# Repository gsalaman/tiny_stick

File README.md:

# Tiny Stick
Hardware design for a line of 8 surface-mount WS2812C LEDs

# Configurations
## UNO (or other external processor)
You can use the 8 RGB LEDs with any Arduino capable processor.  Supply 5v, Gnd, and your Data Input via the "external input" ports on the bottom-left of the board.

You can chain together multiple sticks by using the "external output" port on the bottom-right.
## Tiny85
The board can also be populated with a tiny85.  Recommended configuration is to put a socket on U1 (top left) as to allow for the processor to be removed and programmed.  This processor connects to the data input line via Ardiuno Data pin 3 (physical pin 2 on the tiny).

There is also space on the board for a potentiometer.  The two sides are connected to power and ground, and the middle is connected to arduino pin 2 (physical pin 7).

Finally, there is a push-button, connected to Arduino pin 0 (phyical pin 5).  This input is pulled-up.

## Using External 5v Power with Tiny85
You can connect +5v and GND to the "external input" pins on the bottom left of the board to power the Tiny and LEDs.  This input is *not* gated by the power swiitch.

## Using Coin Cell
The back of the board has a spot for a coin cell holder, which can provide power to the Tiny and LEDs.  To enable this:
* connect the middle and bottom pins of the "input power select" block, either via a jumper or solder blob.
* populate the "internal power" switch on the bottom of the board (for switch control), or, if you want it "always on", put a solder jumper between the left and middle pins.

## Using the 9v (vin) input)
You can connect a 9v battery (or anything greather than 6v) to the Vin jumpers on the bottom left of the board.  This input goes through a voltage regulator to provide 5v.  To enable this:
* connect the top and middle pins of the "input power select" block, either via a jumper or solder blob.
* populate the "internal power" switch on the bottom of the board (for switch control), or, if you want it "always on", put a solder jumper between the left and middle pins.

One note:  since the switch is after the voltage regulator, the 9v battery will *always* be powering on the voltage regulator...not an ideal design.

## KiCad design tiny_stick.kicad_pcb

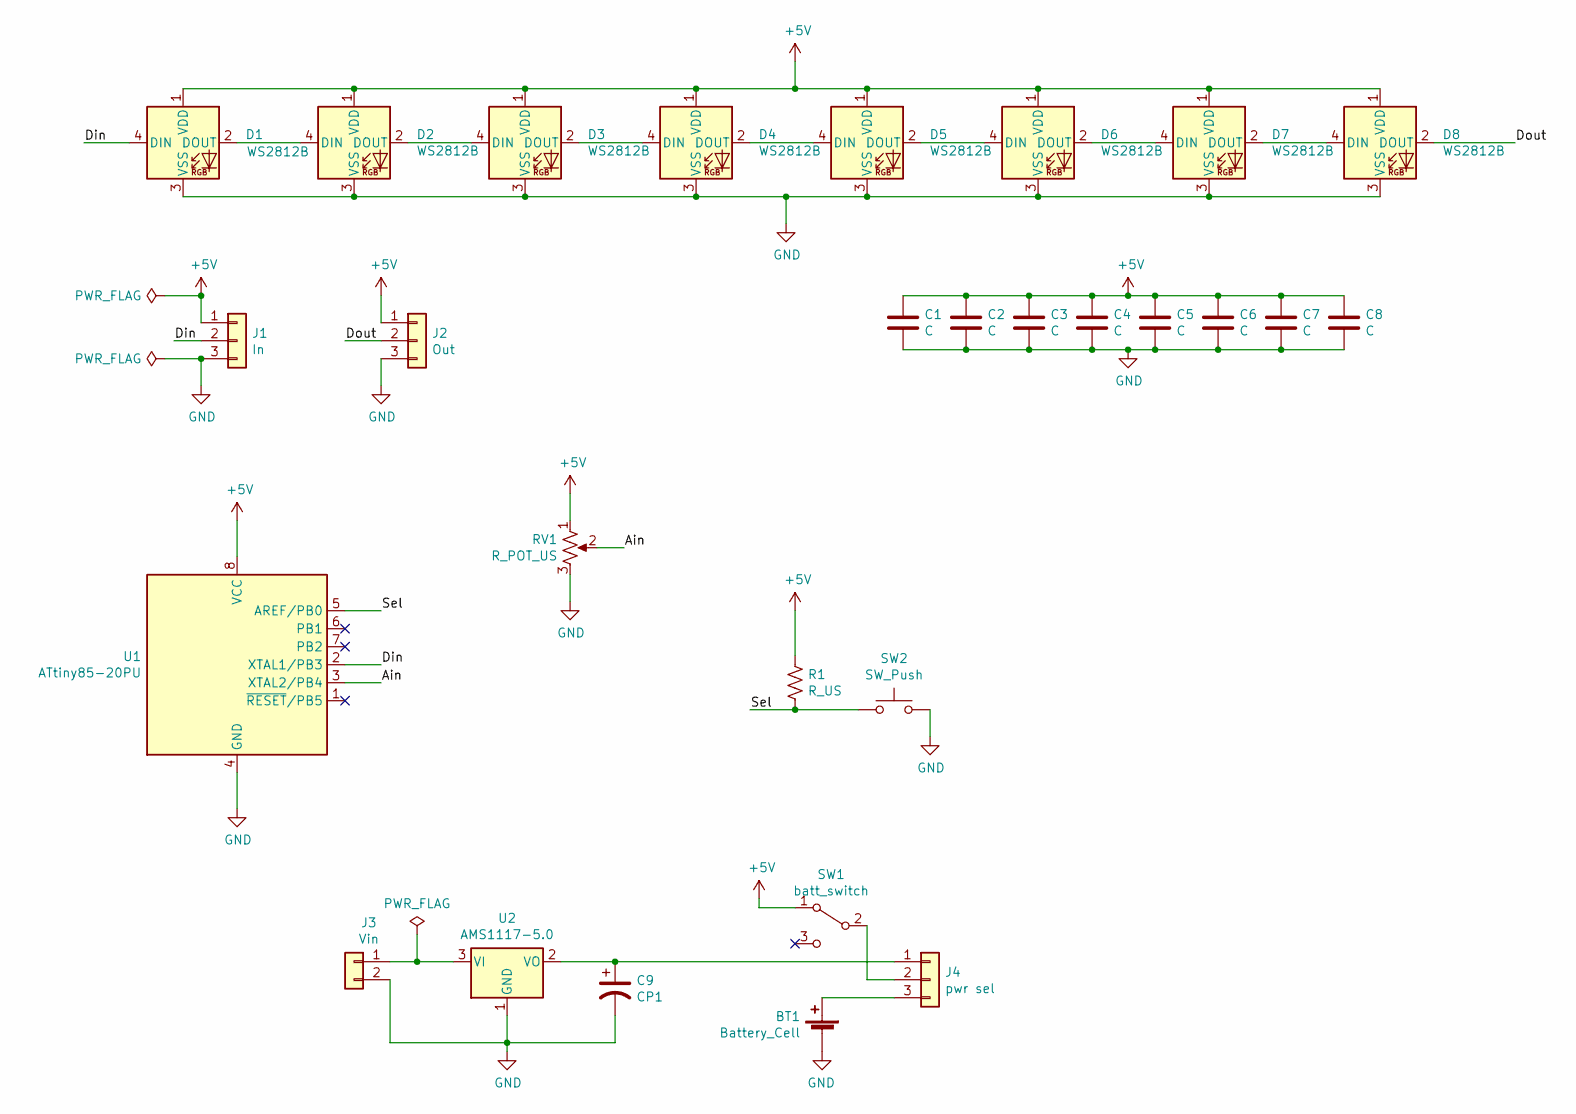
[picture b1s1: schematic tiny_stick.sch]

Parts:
BT1: Battery_Cell; BatteryHolder_Glenn1
C1, C2, C3, C4, C5, C6, C7, C8: C; C_0603_1608Metric
C9: CP1; CP_EIA-3528-21_Kemet-B
D1, D2, D3, D4, D5, D6, D7, D8: WS2812B; LED_WS2812B_PLCC4_5.0x5.0mm_P3.2mm
J1: In; PinHeader_1x03_P2.54mm_Vertical
J2: Out; PinHeader_1x03_P2.54mm_Vertical
J3: Vin; PinHeader_1x02_P2.54mm_Vertical
J4: pwr sel; PinHeader_1x03_P2.54mm_Vertical
R1: R_US; R_0603_1608Metric
RV1: R_POT_US; PinHeader_1x03_P2.54mm_Vertical
SW1: batt_switch; PinHeader_1x03_P2.54mm_Vertical
SW2: SW_Push; SW_PUSH-12mm
U1: ATtiny85-20PU; DIP-8_W7.62mm
U2: AMS1117-5.0; SOT-223-3_TabPin2

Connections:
+5V: C1.1, C2.1, C3.1, C4.1, C5.1, C6.1, C7.1, C8.1, D1.1 (VDD), D2.1 (VDD), D3.1 (VDD), D4.1 (VDD), D5.1 (VDD), D6.1 (VDD), D7.1 (VDD), D8.1 (VDD), J1.1, J2.1, R1.1, RV1.1, SW1.1 (A), U1.8 (VCC)
/Ain: RV1.2, U1.3 (XTAL2/PB4)
/Din: D1.4 (DIN), J1.2, U1.2 (XTAL1/PB3)
/Dout: D8.2 (DOUT), J2.2
/Sel: R1.2, SW2.1, U1.5 (AREF/PB0)
GND: BT1.2 (-), C1.2, C2.2, C3.2, C4.2, C5.2, C6.2, C7.2, C8.2, C9.2, D1.3 (VSS), D2.3 (VSS), D3.3 (VSS), D4.3 (VSS), D5.3 (VSS), D6.3 (VSS), D7.3 (VSS), D8.3 (VSS), J1.3, J2.3, J3.2, RV1.3, SW2.2, U1.4 (GND), U2.1 (GND)
unnamed: BT1.1 (+), J4.3
unnamed: C9.1, J4.1, U2.2 (VO)
unnamed: D1.2 (DOUT), D2.4 (DIN)
unnamed: D2.2 (DOUT), D3.4 (DIN)
unnamed: D3.2 (DOUT), D4.4 (DIN)
unnamed: D4.2 (DOUT), D5.4 (DIN)
unnamed: D5.2 (DOUT), D6.4 (DIN)
unnamed: D6.2 (DOUT), D7.4 (DIN)
unnamed: D7.2 (DOUT), D8.4 (DIN)
unnamed: J3.1, U2.3 (VI)
unnamed: J4.2, SW1.2 (B)

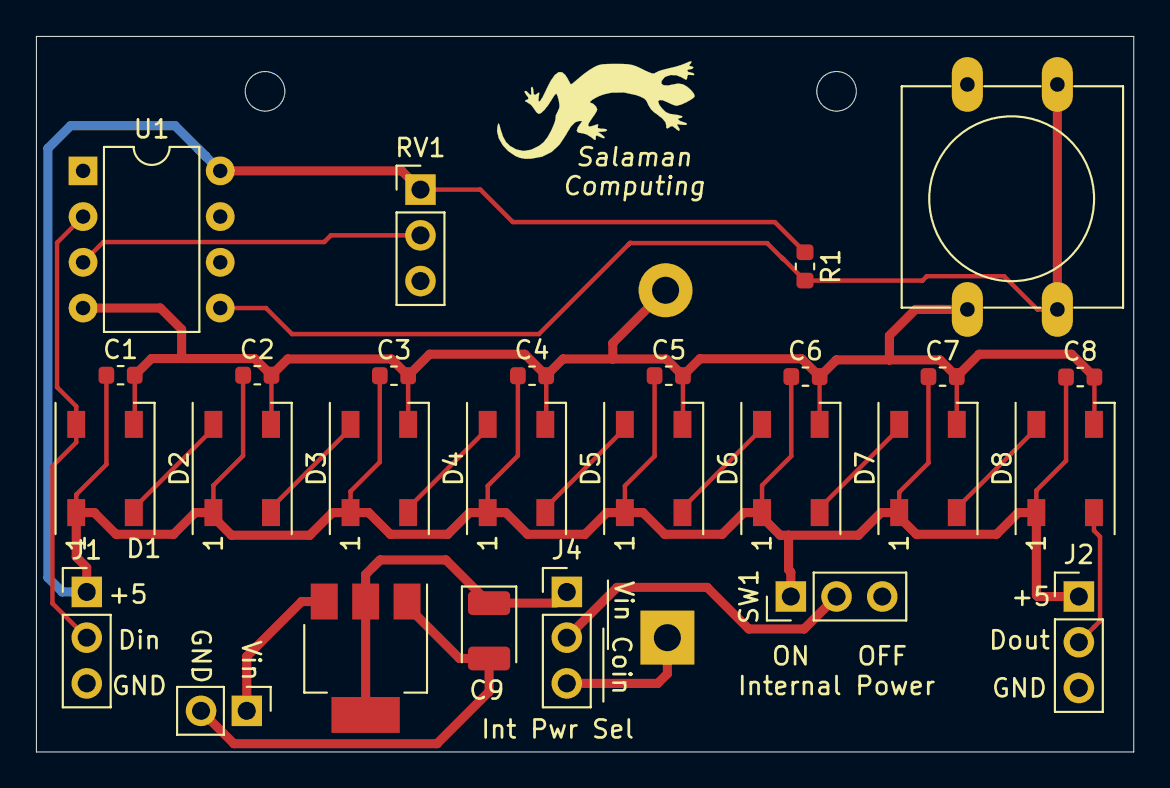
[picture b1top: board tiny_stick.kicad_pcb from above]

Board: 2 copper layers, 61.0 x 39.8 mm, 28 parts (1 on the bottom side), 17 nets.

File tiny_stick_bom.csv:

Comment,Designator,Footprint,LCSC Part Number2812 LED,"D1,D2,D3,D4,D5,D6,D7,D8",LED-4_5050,C1145864.7k ohm,R1,603,C2316222uF Tant,C9,CASE-B_3528,C110051AMS1117-5.0,U2,SOT-223,C6187.1 uF ,"C1,C2,C3,C4,C5,C6,C7,C8",603,C14663

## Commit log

2020-01-28 Updated with production files
